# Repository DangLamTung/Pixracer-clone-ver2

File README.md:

# Pixracer_clone

 Open source flight controller based on the Pixracer flight controller.
 
 The  object of this project is to utilize the spare part I have :))) 
 
 The Flight controller using 36.5*36.5 FPV racing size, nowaday I think this is the most popular and flexible size for both FPV quadcopter and small-sized fixed wing.
 
 To make the soldering process easier, I used the smallest footprint is 0603, which can hand-solderable.
 
 This board will be mainly running Ardupilot firmware, but in the future I will test it with Betaflight and Inav
 
 This flight controller included these feature:

     +  STM32F429VIT6 microcontroller
     +  ICM20689 IMU 
     +  BMP280 barometer
     +  AT7456E OSD chip
     +  TPS5430 buck converter 5V output
     +  10 PWM outputs 
     +  5 UART, 2 I2C and 2 SPI pinout
     +  Built in voltage divider for battery monitoring
What can be improve?
     +  The original Pixracer dont have OSD chip for analog FPV, this may not be important in the future, because the development of recent digital FPV system, but I add a OSD anyway,
     +  The built in buck converter is 5V only, because of space constraint and to make the board atleast hand solderable, I didn't add a 9V buck, this is not ideal for using with 
     HD FPV system, I will add a 9V buck converter in the future.
     +  An ESP-32 or NRF52 wifi or bluetooth would be very nice to have in the next version :)))

Updaded the Inav  firmware and target

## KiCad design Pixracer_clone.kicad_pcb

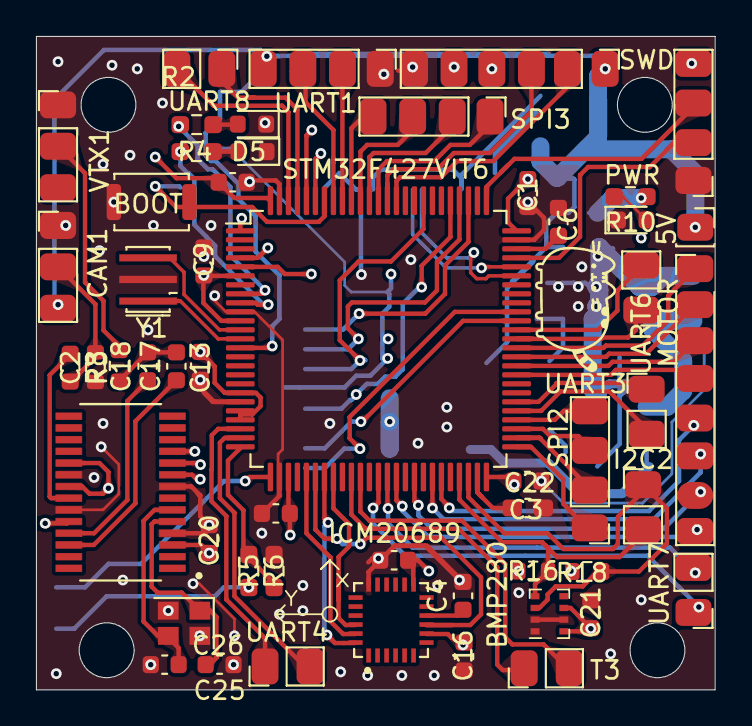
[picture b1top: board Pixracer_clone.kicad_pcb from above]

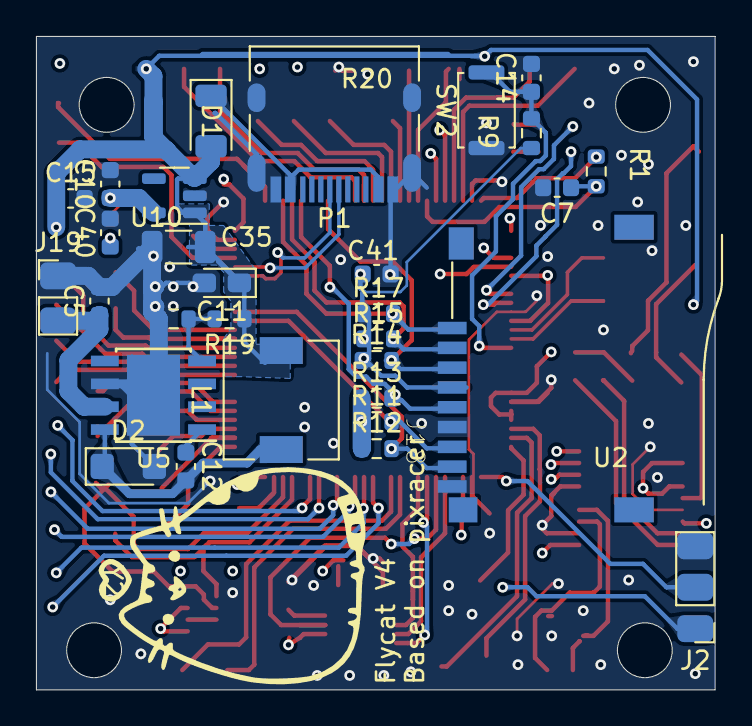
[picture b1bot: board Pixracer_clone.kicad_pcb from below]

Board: 4 copper layers, 37.7 x 36.3 mm, 83 parts (30 on the bottom side), 84 nets.

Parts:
5V: Conn_01x01_Pin; PinSocket_1x01_P2.00mm_Vertical
BMP280: BMP280; Bosch_LGA-8_2x2.5mm_P0.65mm_ClockwisePinNumbering
BOOT: SW_Push; SW_Push_SPST_NO_Alps_SKRK
C1: CP; C_0603_1608Metric
C2, C17, C25: 47uF; C_0603_1608Metric
C3: CP; C_0603_1608Metric_Pad1.08x0.95mm_HandSolder
C4, C16, C21, C23: 0.1uF; C_0603_1608Metric
C5, C6, C7, C8, C9, C13, C14, C19, C20, C22, C40: 100n; C_0603_1608Metric
C10: 1u; C_0603_1608Metric
C11: 220uF; CP_EIA-2012-15_AVX-P_Pad1.30x1.05mm_HandSolder
C12: 0.01uF; C_0603_1608Metric
C15, C41: C; C_0603_1608Metric
C18, C26: 22uF; C_0603_1608Metric
C35: CP; C_1206_3216Metric
CAM1: Conn_01x03_Male; PinHeader_1x03_P2.00mm_Vertical
D1: DIODE; D_1206_3216Metric
D2: B340; D_SMF
D4, D5: LED; LED_0603_1608Metric
GPS1: GPS; PinHeader_1x06_P2.00mm_Vertical
I2C2: Conn_01x02_Male; PinHeader_1x02_P2.00mm_Vertical
ICM20689: ICM-20689; QFN50P400X400X95-24N
J2: Conn_01x03_Pin; PinHeader_1x03_P2.00mm_Vertical
J18: Micro_SD_Card; SUNTECH_ST-TF-003A
J19: Conn_01x02_Pin; PinHeader_1x02_P2.00mm_Vertical
L1: 18uH; L_6.3x6.3_H3
MOTOR: Conn_01x08_Male; PinHeader_1x08_P2.00mm_Vertical
P1: USB_C_Plug_USB2.0; USB_C_Receptacle_HRO_TYPE-C-31-M-12
PWR: LED; LED_0603_1608Metric
R1, R9, R11, R12, R13, R14, R15, R16, R17, R18: R; R_0603_1608Metric
R2, R4, R10: R; R_0603_1608Metric_Pad0.98x0.95mm_HandSolder
R3, R8: 75R; R_0603_1608Metric
R5, R6: 10k; R_0603_1608Metric_Pad0.98x0.95mm_HandSolder
R19: 10kOhm; R_0603_1608Metric
R20: 3.24kOhm; R_0603_1608Metric
SPI2, SPI3: SPI3_Conn; PinHeader_1x04_P2.00mm_Vertical
STM32F427VIT6: STM32F427VITx; LQFP-100_14x14mm_P0.5mm
SW2: SW_Push; SW_Push_SPST_NO_Alps_SKRK
SWD: UART4_con; PinHeader_1x04_P2.00mm_Vertical
T3: Conn_01x02_Male; PinHeader_1x02_P2.00mm_Vertical
U2: MAX7456EUI+; SOP65P637X110-28N
U5: TPS5430DDA; TI_SO-PowerPAD-8_ThermalVias
U10: LP5907MFX-3.3; SOT-23-5
UART1: CRSF; PinHeader_1x04_P2.00mm_Vertical
UART3, UART4, UART6, UART7, UART8: Conn_01x02_Male; PinHeader_1x02_P2.00mm_Vertical
VTX1: Conn_01x03_Male; PinHeader_1x03_P2.00mm_Vertical
Y1: Resonator; Resonator_SMD_Murata_CSTxExxV-3Pin_3.0x1.1mm_HandSoldering
Y2: Crystal_GND24_Small; Crystal_SMD_2520-4Pin_2.5x2.0mm

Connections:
5V_IN: 5V.1, C11.1, C15.1, C35.1, CAM1.3, D1.2 (A), GPS1.1, L1.2, R19.1, U10.1 (IN), U10.3 (EN), UART1.4
BATT_CURRENT_SENSE: J2.2, STM32F427VIT6.26 (PA3)
BATT_VOLT: J2.1, R5.1
BATT_VOLT_SENSE: R5.2, R6.1, STM32F427VIT6.25 (PA2)
BOOT0: BOOT.2, C7.1, R1.2, STM32F427VIT6.94 (BOOT0)
GND: BMP280.1 (GND), BMP280.2 (CSB), BMP280.7 (GND), BOOT.1, C1.2, C3.2, C4.2, C5.2, C6.2, C7.2, C8.2, C9.2, C10.2, C11.2, C13.2, C14.2, C15.2, C16.2, C19.2, C20.2, C21.2, C22.2, C23.2, C25.1, C26.1, C35.2, C40.2, C41.2, CAM1.1, D2.2 (A), D4.1 (K), D5.1 (K), GPS1.6, ICM20689.18 (GND), J2.3, J18.6 (VSS), J18.9 (SHIELD), J19.1, P1.A1 (GND), P1.A12 (GND), P1.B1 (GND), P1.B12 (GND), P1.S1 (SHIELD), PWR.1 (K), R3.1, R6.2, R20.2, STM32F427VIT6.10 (VSS), STM32F427VIT6.20 (VSSA), STM32F427VIT6.27 (VSS), STM32F427VIT6.74 (VSS), STM32F427VIT6.99 (VSS), SW2.1, SWD.1, U2.4 (DGND), U2.8 (~CS), U2.20 (AGND), U2.23 (PGND), U5.6 (GND), U5.9 (GNDPAD), U10.2 (GND), UART1.1, VTX1.1, Y1.2, Y2.2, Y2.4
I2C2_SCl: BMP280.4 (SCK), I2C2.2, R16.2, STM32F427VIT6.47 (PB10)
I2C2_SDA: BMP280.3 (SDI), I2C2.1, R18.2, STM32F427VIT6.48 (PB11)
I2C_SCl: GPS1.4, STM32F427VIT6.95 (PB8)
I2C_SDA: GPS1.5, STM32F427VIT6.96 (PB9)
IMU_CLK: ICM20689.23 (SCL/SCLK), STM32F427VIT6.30 (PA5)
IMU_MISO: ICM20689.9 (AD0/SDO), STM32F427VIT6.31 (PA6)
IMU_MOSI: ICM20689.24 (SDA/SDI), STM32F427VIT6.32 (PA7)
LED2: R2.1, STM32F427VIT6.8 (PC14)
LED3: R4.1, STM32F427VIT6.9 (PC15)
MISO_OSD: STM32F427VIT6.4 (PE5), U2.11 (SDOUT)
MOSI_OSD: STM32F427VIT6.5 (PE6), U2.9 (SDIN)
MPU9250_CS: ICM20689.22 (NCS), STM32F427VIT6.33 (PC4)
NRST: C14.1, R9.2, STM32F427VIT6.14 (NRST), SW2.2
unnamed: C17.2, C18.2, R8.1
unnamed: C12.2, D2.1 (K), L1.1, U5.8 (PH)
unnamed: D4.2 (A), R2.2
unnamed: D5.2 (A), R4.2
unnamed: PWR.2 (A), R10.2
unnamed: C4.1, ICM20689.10 (REGOUT)
unnamed: C25.2, U2.5 (CLKIN), Y2.1
unnamed: C18.1, U2.25 (SAG)
unnamed: C2.2, U2.22 (VIN)
unnamed: C17.1, U2.26 (VOUT)
unnamed: C26.2, U2.6 (XFB), Y2.3
unnamed: C12.1, U5.1 (BOOT)
unnamed: R19.2, R20.1, U5.4 (VSENSE)
OSC1+: STM32F427VIT6.12 (PH0), Y1.3
OSC1-: STM32F427VIT6.13 (PH1), Y1.1
OSD_VIDEO_IN: C2.1, CAM1.2, R3.2
OSD_VIDEO_OUT: R8.2, VTX1.2
PWR_IN: C5.1, J19.2, U5.7 (VIN), VTX1.3
SBUS: STM32F427VIT6.24 (PA1), UART4.2
SCLK_OSD: STM32F427VIT6.1 (PE2), U2.10 (SCLK)
SDIO0: J18.7 (DAT0), R11.2, STM32F427VIT6.65 (PC8)
SDIO1: J18.8 (DAT1), R12.2, STM32F427VIT6.66 (PC9)
SDIO2: J18.1 (DAT2), R17.2, STM32F427VIT6.78 (PC10)
SDIO3: J18.2 (DAT3/CD), R15.2, STM32F427VIT6.79 (PC11)
SDIO_CLK: J18.5 (CLK), R13.2, STM32F427VIT6.80 (PC12)
SDIO_CMD: J18.3 (CMD), R14.2, STM32F427VIT6.83 (PD2)
SPI2_CS: SPI2.1, STM32F427VIT6.51 (PB12)
SPI2_MISO: SPI2.3, STM32F427VIT6.53 (PB14)
SPI2_MOSI: SPI2.4, STM32F427VIT6.54 (PB15)
SPI2_SCK: SPI2.2, STM32F427VIT6.52 (PB13)
SPI3_CS: SPI3.1, STM32F427VIT6.88 (PD7)
SPI3_MISO: SPI3.3, STM32F427VIT6.90 (PB4)
SPI3_MOSI: SPI3.4, STM32F427VIT6.91 (PB5)
SPI3_SCK: SPI3.2, STM32F427VIT6.89 (PB3)
SWCLK: STM32F427VIT6.76 (PA14), SWD.3
SWDIO: STM32F427VIT6.72 (PA13), SWD.2
TIM1_CH1: MOTOR.8, STM32F427VIT6.40 (PE9)
TIM1_CH2: MOTOR.7, STM32F427VIT6.42 (PE11)
TIM1_CH3: MOTOR.6, STM32F427VIT6.44 (PE13)
TIM1_CH4: MOTOR.5, STM32F427VIT6.45 (PE14)
TIM3_CH3: STM32F427VIT6.35 (PB0), T3.1
TIM3_CH4: STM32F427VIT6.36 (PB1), T3.2
TIM4_CH1: MOTOR.4, STM32F427VIT6.59 (PD12)
TIM4_CH2: MOTOR.3, STM32F427VIT6.60 (PD13)
TIM4_CH3: MOTOR.2, STM32F427VIT6.61 (PD14)
TIM4_CH4: MOTOR.1, STM32F427VIT6.62 (PD15)
UART1_RX: STM32F427VIT6.93 (PB7), UART1.3
UART1_TX: STM32F427VIT6.92 (PB6), UART1.2
UART2_RX: GPS1.3, STM32F427VIT6.87 (PD6)
UART2_TX: GPS1.2, STM32F427VIT6.86 (PD5)
UART3_RX: STM32F427VIT6.55 (PD8), UART3.2
UART3_TX: STM32F427VIT6.56 (PD9), UART3.1
UART4_TX: STM32F427VIT6.23 (PA0), UART4.1
UART6_RX: STM32F427VIT6.64 (PC7), UART6.2
UART6_TX: STM32F427VIT6.63 (PC6), UART6.1
UART7_RX: STM32F427VIT6.38 (PE7), UART7.1
UART7_TX: STM32F427VIT6.39 (PE8), UART7.2
UART8_RX: STM32F427VIT6.97 (PE0), UART8.1
UART8_TX: STM32F427VIT6.98 (PE1), UART8.2
USB_D+: P1.A6 (D+), STM32F427VIT6.71 (PA12)
USB_D-: P1.A7 (D-), STM32F427VIT6.70 (PA11)
VBUS: D1.1 (K), P1.A4 (VBUS), P1.A9 (VBUS), P1.B4 (VBUS), P1.B9 (VBUS)
VCAP_1: C3.1, STM32F427VIT6.49 (VCAP_1)
VCAP_2: C1.1, STM32F427VIT6.73 (VCAP_2)
VCC: BMP280.6 (VDDIO), BMP280.8 (VDD), C6.1, C8.1, C9.1, C10.1, C13.1, C16.1, C19.1, C20.1, C21.1, C22.1, C23.1, C40.1, C41.1, ICM20689.8 (VDDIO), ICM20689.13 (VDD), J18.4 (VDD), R1.1, R9.1, R10.1, R11.1, R12.1, R13.1, R14.1, R15.1, R16.1, R17.1, R18.1, STM32F427VIT6.6 (VBAT), STM32F427VIT6.11 (VDD), STM32F427VIT6.19 (VDD), STM32F427VIT6.21 (VREF+), STM32F427VIT6.22 (VDDA), STM32F427VIT6.28 (VDD), STM32F427VIT6.50 (VDD), STM32F427VIT6.75 (VDD), STM32F427VIT6.100 (VDD), SWD.4, U2.3 (DVDD), U2.19 (~RESET), U2.21 (AVDD), U2.24 (PVDD), U10.5 (OUT)

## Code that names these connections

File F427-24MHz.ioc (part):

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Mcu.Name=STM32F427V(G-I)Tx
Mcu.Package=LQFP100
Mcu.UserName=STM32F427VITx
PA0/WKUP.Mode=Asynchronous
PA0/WKUP.Signal=UART4_TX
PA1.Mode=Asynchronous
PA1.Signal=UART4_RX
PA10.Mode=Asynchronous
PA10.Signal=USART1_RX
PA11.Mode=Device_Only
PA11.Signal=USB_OTG_FS_DM
PA12.Mode=Device_Only
PA12.Signal=USB_OTG_FS_DP
PA13.Mode=Serial_Wire
PA13.Signal=SYS_JTMS-SWDIO
PA14.Mode=Serial_Wire
PA14.Signal=SYS_JTCK-SWCLK
PA2.Signal=ADCx_IN2
PA3.Signal=ADCx_IN3
PA4.Signal=ADCx_IN4
PA5.Mode=Full_Duplex_Master
PA5.Signal=SPI1_SCK
PA6.Mode=Full_Duplex_Master
PA6.Signal=SPI1_MISO
PA7.Mode=Full_Duplex_Master
PA7.Signal=SPI1_MOSI
PA8.Mode=Clock-out-1
PA8.Signal=RCC_MCO_1
PA9.Mode=Asynchronous
PA9.Signal=USART1_TX
PB0.Signal=GPIO_Output
PB1.Signal=GPIO_Output
PB10.Mode=I2C
PB10.Signal=I2C2_SCL
PB11.Mode=I2C
PB11.Signal=I2C2_SDA
PB12.Signal=GPIO_Output
PB13.Mode=Full_Duplex_Master
PB13.Signal=SPI2_SCK
PB14.Mode=Full_Duplex_Master
PB14.Signal=SPI2_MISO
PB15.Mode=Full_Duplex_Master
PB15.Signal=SPI2_MOSI
PB2/BOOT1.Signal=GPIO_Output
PB3.Mode=Full_Duplex_Master
PB3.Signal=SPI3_SCK
PB4.Mode=Full_Duplex_Master
PB4.Signal=SPI3_MISO
PB5.Mode=Full_Duplex_Master
PB5.Signal=SPI3_MOSI
PB6.Mode=I2C
PB6.Signal=I2C1_SCL
PB7.Mode=I2C
PB7.Signal=I2C1_SDA
PC10.Mode=SD_4_bits_Wide_bus
PC10.Signal=SDIO_D2
PC11.Mode=SD_4_bits_Wide_bus
PC11.Signal=SDIO_D3
PC12.Mode=SD_4_bits_Wide_bus
PC12.Signal=SDIO_CK
PC4.Signal=GPIO_Output
PC5.Signal=GPIO_Output
PC6.Mode=Asynchronous
PC6.Signal=USART6_TX
PC7.Mode=Asynchronous
PC7.Signal=USART6_RX
PC8.Mode=SD_4_bits_Wide_bus
PC8.Signal=SDIO_D0
PC9.Mode=SD_4_bits_Wide_bus
PC9.Signal=SDIO_D1
PD0.Mode=Master
PD0.Signal=CAN1_RX
PD1.Mode=Master
PD1.Signal=CAN1_TX
PD12.Signal=S_TIM4_CH1
PD13.Signal=S_TIM4_CH2
PD14.Signal=S_TIM4_CH3
PD15.Signal=S_TIM4_CH4
PD2.Mode=SD_4_bits_Wide_bus
PD2.Signal=SDIO_CMD
PD3.Mode=CTS_RTS
PD3.Signal=USART2_CTS
PD4.Mode=CTS_RTS
PD4.Signal=USART2_RTS
PD5.Mode=Asynchronous
PD5.Signal=USART2_TX
PD6.Mode=Asynchronous
PD6.Signal=USART2_RX
PD8.Mode=Asynchronous
PD8.Signal=USART3_TX
PD9.Mode=Asynchronous
PD9.Signal=USART3_RX
PE0.Mode=Asynchronous
PE0.Signal=UART8_RX
PE1.Mode=Asynchronous
PE1.Signal=UART8_TX
PE11.Signal=S_TIM1_CH2
PE13.Signal=S_TIM1_CH3
PE14.Signal=S_TIM1_CH4
PE2.Mode=Full_Duplex_Master
PE2.Signal=SPI4_SCK
PE5.Mode=Full_Duplex_Master
PE5.Signal=SPI4_MISO
PE6.Mode=Full_Duplex_Master
PE6.Signal=SPI4_MOSI
PE7.Mode=Asynchronous
PE7.Signal=UART7_RX
PE8.Mode=Asynchronous
PE8.Signal=UART7_TX
PE9.Signal=S_TIM1_CH1
PH0/OSC_IN.Mode=HSE-External-Oscillator
PH0/OSC_IN.Signal=RCC_OSC_IN
PH1/OSC_OUT.Mode=HSE-External-Oscillator
PH1/OSC_OUT.Signal=RCC_OSC_OUT
RCC.HSE_VALUE=24000000
RCC.SYSCLKFreq_VALUE=168000000
RCC.SYSCLKSource=RCC_SYSCLKSOURCE_PLLCLK
board=custom
